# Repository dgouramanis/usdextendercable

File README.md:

# micro SD card extension cord
I designed this little tool while compiling a software installation on BeagleBone Black. I needed to repetitively remove/inset the micro uSD card. The BeagleBone was installed in a hard-to-reach area. So much time was wasted trying to inset the card with tweezers. 

This simple tool plugs into the hard-to-reach socket, and provides a flexible extension.

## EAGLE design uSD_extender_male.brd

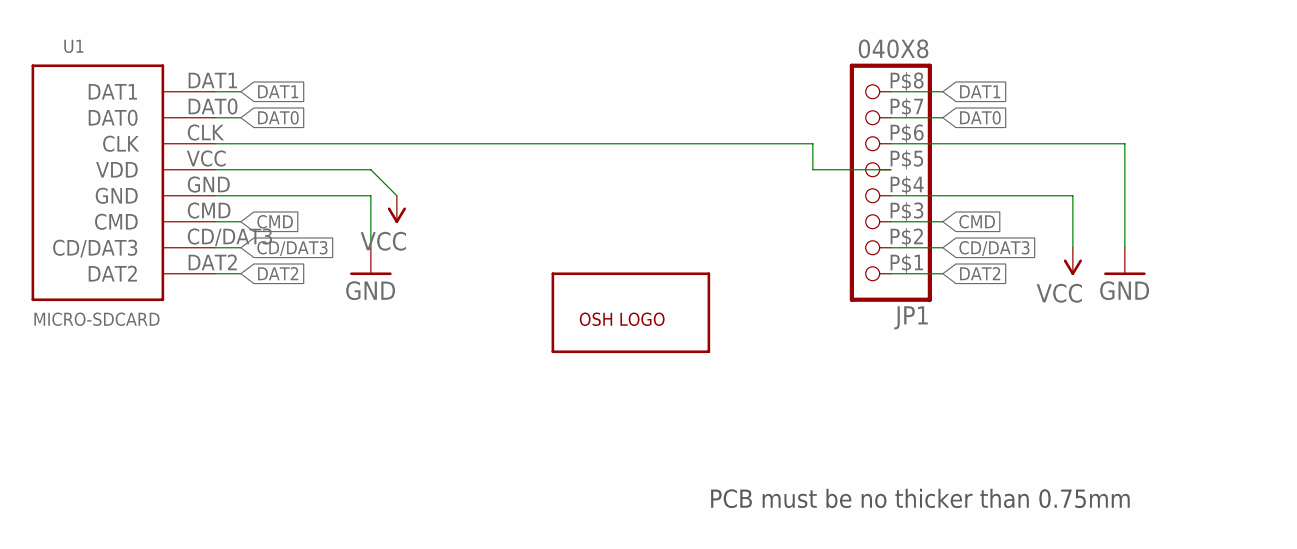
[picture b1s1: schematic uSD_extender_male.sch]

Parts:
JP1: 040X8
U1: MICRO-SDCARD
U$1: OSH_LOGO

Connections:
CD/DAT3: JP1.P$2 (2), U1.CD/DAT3
CMD: JP1.P$3 (3), U1.CMD
DAT0: JP1.P$7 (7), U1.DAT0
DAT1: JP1.P$8 (8), U1.DAT1
DAT2: JP1.P$1 (1), U1.DAT2
GND: JP1.P$6 (6), U1.GND
unnamed: JP1.P$5 (5), U1.CLK
VCC: JP1.P$4 (4), U1.VCC (VDD)

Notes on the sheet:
PCB must be no thicker than 0.75mm

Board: 2 copper layers, 3 parts (1 on the bottom side), 8 nets.

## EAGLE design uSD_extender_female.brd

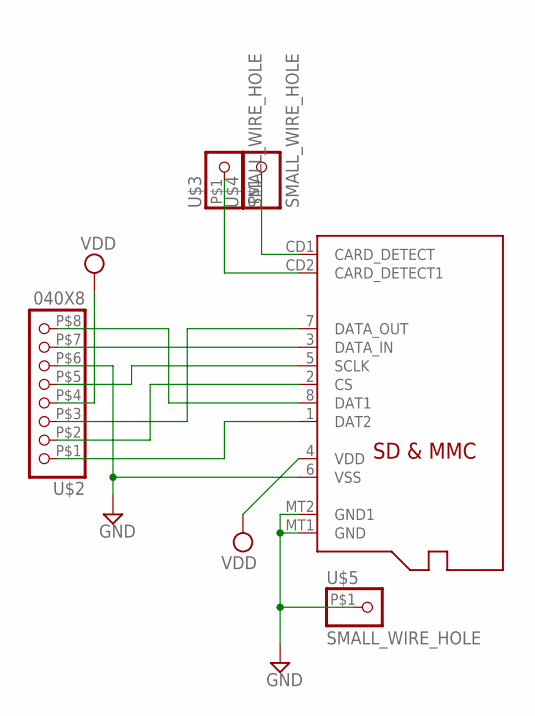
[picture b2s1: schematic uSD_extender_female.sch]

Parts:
U$1: MICROSD
U$2: 040X8
U$3, U$4, U$5: SMALL_WIRE_HOLE

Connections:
GND: U$1.MT1 (GND), U$1.MT2 (GND1), U$5.P$1
unnamed: U$1.5 (SCLK), U$2.P$5 (5)
unnamed: U$1.2 (CS), U$2.P$2 (2)
unnamed: U$1.1 (DAT2), U$2.P$1 (1)
unnamed: U$1.8 (DAT1), U$2.P$8 (8)
unnamed: U$1.7 (DATA_OUT), U$2.P$7 (7)
unnamed: U$1.3 (DATA_IN), U$2.P$3 (3)
unnamed: U$1.CD1 (CARD_DETECT), U$4.P$1
unnamed: U$1.CD2 (CARD_DETECT1), U$3.P$1
VDD: U$1.4 (VDD), U$2.P$4 (4)
VSS: U$1.6 (VSS), U$2.P$6 (6)

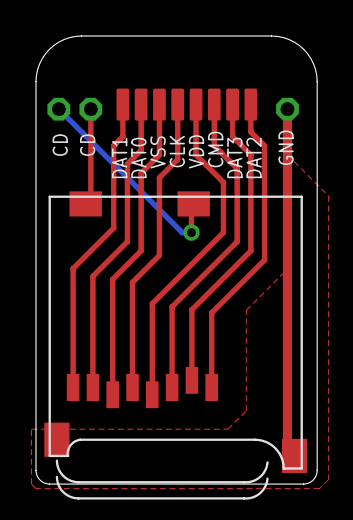
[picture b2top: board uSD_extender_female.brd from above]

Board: 2 copper layers, 15.6 x 24.9 mm, 5 parts (0 on the bottom side), 11 nets.

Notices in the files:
parts and their libraries:
SparkFun-Boards: Licensing: Creative Commons ShareAlike 4.0 International - https://creativecommons.org/licenses/by-sa/4.0
